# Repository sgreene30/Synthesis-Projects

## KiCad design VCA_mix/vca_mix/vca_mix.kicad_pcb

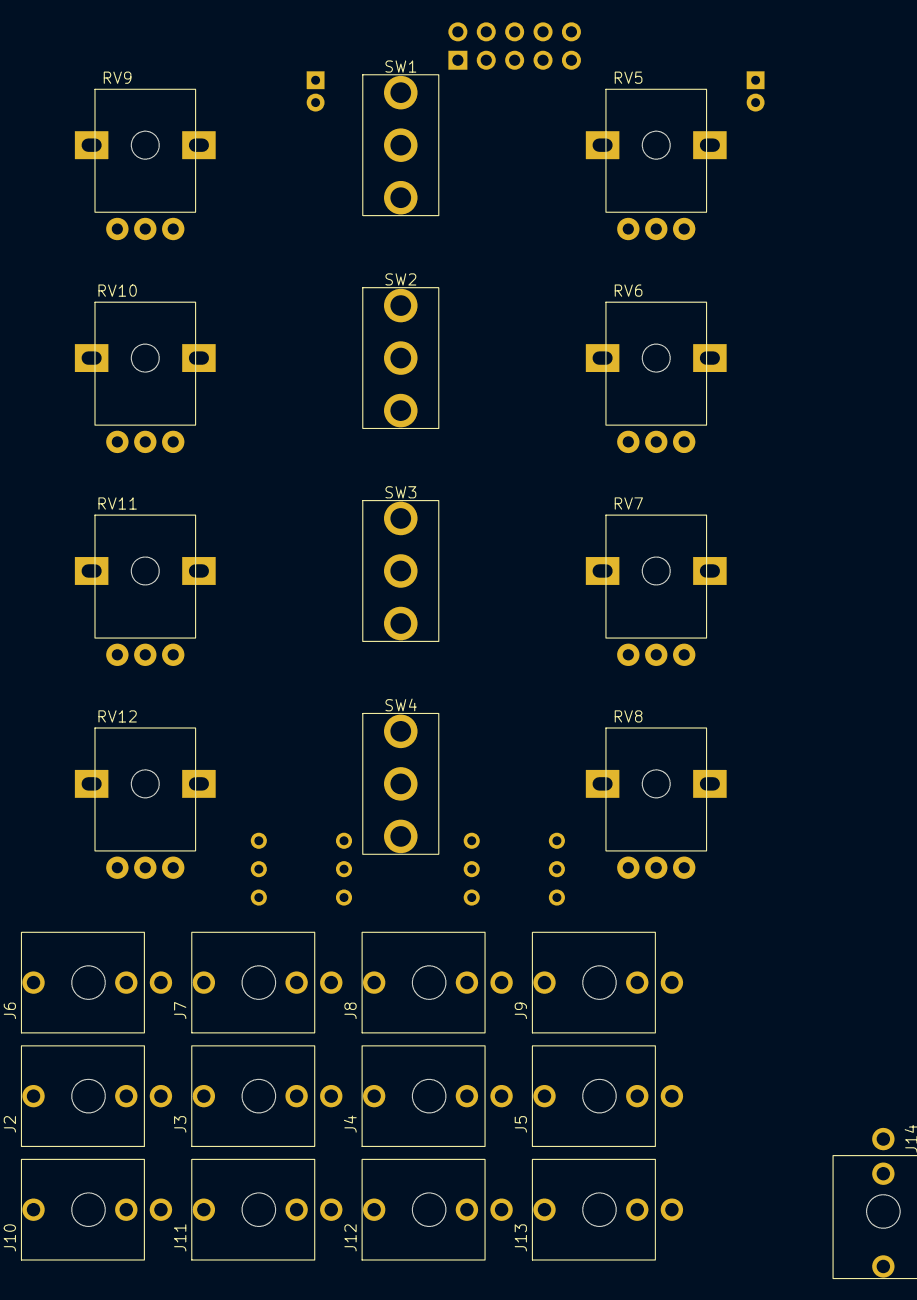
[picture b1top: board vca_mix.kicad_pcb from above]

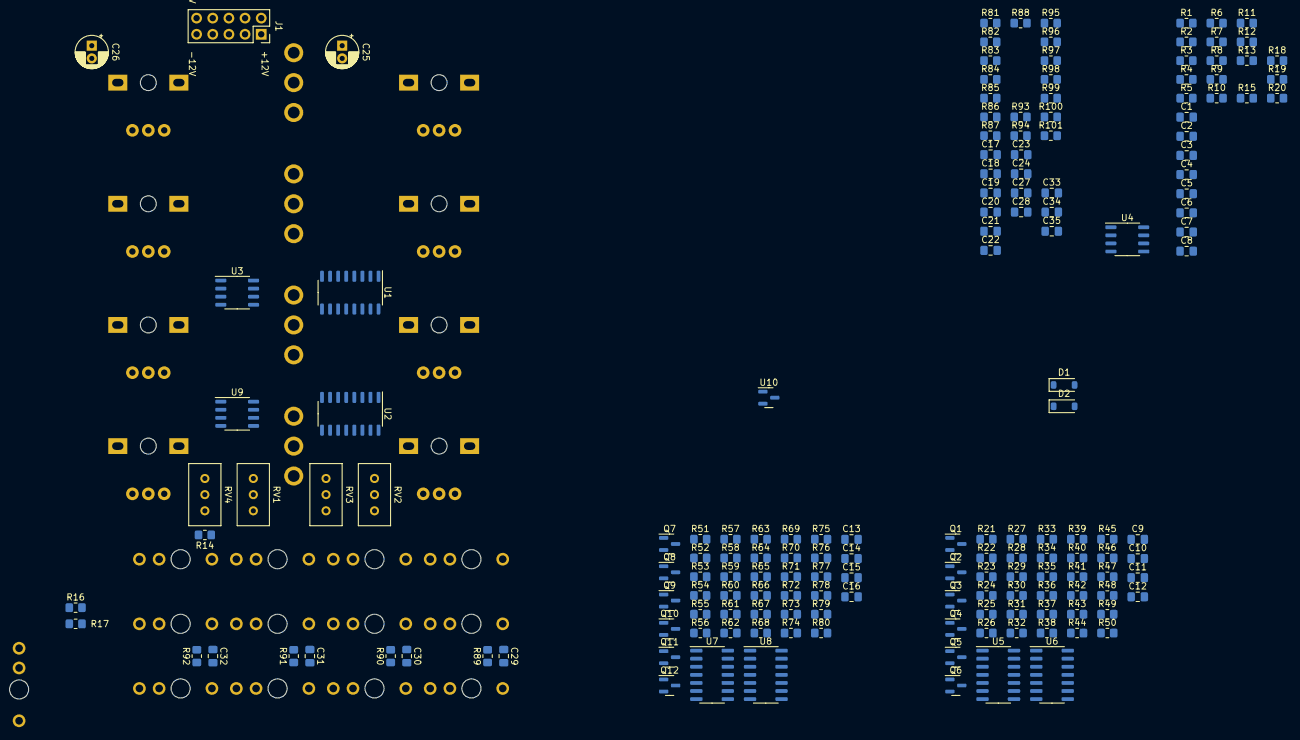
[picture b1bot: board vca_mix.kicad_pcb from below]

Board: 2 copper layers, 190 parts (165 on the bottom side), 128 nets, no tracks yet.

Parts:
C1, C2, C3, C4, C5, C6, C7, C8, C9, C10, C11, C12, C13, C14, C15, C16, C27, C28: 100n; C_0805_2012Metric_Pad1.18x1.45mm_HandSolder
C17, C18, C19, C20, C21, C22, C23, C24, C29, C30, C31, C32, C33: DNP; C_0805_2012Metric_Pad1.18x1.45mm_HandSolder
C25, C26: 10u; CP_Radial_D5.0mm_P2.00mm
C34, C35: 100p; C_0805_2012Metric_Pad1.18x1.45mm_HandSolder
D1: MBR0530-TP; D_SOD-123
D2: D_Schottky; D_SOD-123
J1: power; PinSocket_2x05_P2.54mm_Vertical
J2, J3, J4, J5, J6, J7, J8, J9, J10, J11, J12, J13, J14: Thonkiconn; thonkiconn
Q1, Q5, Q8, Q11: MMBT3904; SOT-23
Q2, Q3, Q4, Q6, Q7, Q9, Q10, Q12: MMBT3906; SOT-23
R1, R2, R11, R14, R31, R32, R34, R37, R46, R49, R52, R61, R64, R67, R76, R79, R98, R99: 20k; R_0805_2012Metric_Pad1.20x1.40mm_HandSolder
R3, R4, R5, R6, R12, R13, R16, R17: 430R; R_0805_2012Metric_Pad1.20x1.40mm_HandSolder
R7, R8, R15, R18, R24, R25, R28, R35, R39, R41, R48, R50, R54, R56, R63, R65, R69, R71, R78, R80, R94, R95, R96, R97, R100: 10k; R_0805_2012Metric_Pad1.20x1.40mm_HandSolder
R9, R10, R19, R20: 47k; R_0805_2012Metric_Pad1.20x1.40mm_HandSolder
R21, R23, R26, R38, R42, R45, R53, R57, R60, R68, R72, R75: 200k; R_0805_2012Metric_Pad1.20x1.40mm_HandSolder
R22, R43, R58, R73: 100k; R_0805_2012Metric_Pad1.20x1.40mm_HandSolder
R27, R44, R59, R74: 3k; R_0805_2012Metric_Pad1.20x1.40mm_HandSolder
R29, R40, R55, R70: 330; R_0805_2012Metric_Pad1.20x1.40mm_HandSolder
R30, R47, R62, R77: 120k; R_0805_2012Metric_Pad1.20x1.40mm_HandSolder
R33, R36, R51, R66: 6k2; R_0805_2012Metric_Pad1.20x1.40mm_HandSolder
R81, R82, R83, R84, R85, R86, R87, R88: 0R; R_0805_2012Metric_Pad1.20x1.40mm_HandSolder
R89, R90, R91, R92, R93: 100R; R_0805_2012Metric_Pad1.20x1.40mm_HandSolder
R101: 470; R_0805_2012Metric_Pad1.20x1.40mm_HandSolder
RV1, RV2, RV3, RV4: 100R; Potentiometer_Bourns_3296W_Vertical
RV5, RV6, RV7, RV8, RV9, RV10, RV11, RV12: 10k; alpha_pot
SW1, SW2, SW3, SW4: SW_SPDT; Mini_sw
U1, U2: LM13700; SO-16_3.9x9.9mm_P1.27mm
U3, U4, U9: TL072; SO-8_3.9x4.9mm_P1.27mm
U5, U6, U7, U8: TL074; SO-14_3.9x8.65mm_P1.27mm
U10: LM4040DBZ-3; SOT-23

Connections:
+3V0: R28.1, R33.1, R36.1, R39.1, R51.1, R54.1, R66.1, R69.1, R101.2, U10.1 (K)
+12V: C1.1, C3.1, C5.1, C7.1, C9.1, C11.1, C13.1, C15.1, C25.1, C27.1, D1.1 (K), Q1.3 (C), Q5.3 (C), Q8.3 (C), Q11.3 (C), R7.2, R8.2, R15.2, R18.2, R101.1, RV5.1, RV6.1, RV7.1, RV8.1, U1.11 (V+), U2.11 (V+), U3.8 (V+), U4.8 (V+), U5.4 (V+), U6.4 (V+), U7.4 (V+), U8.4 (V+), U9.8 (V+)
-12V: C2.2, C4.2, C6.2, C8.2, C10.2, C12.2, C14.2, C16.2, C26.2, C28.2, D2.2 (A), R30.1, R47.1, R62.1, R77.1, RV5.3, RV6.3, RV7.3, RV8.3, U1.6 (V-), U2.6 (V-), U3.4 (V-), U4.4 (V-), U5.11 (V-), U6.11 (V-), U7.11 (V-), U8.11 (V-), U9.4 (V-)
/IO/MIX_OUT: C33.1, C35.2, R93.2, R100.2, U9.7
/IO/VCA_1_MIX: J10.TN, R94.1
/IO/VCA_2_MIX: J11.TN, R95.1
/IO/VCA_3_MIX: J12.TN, R96.1
/IO/VCA_4_MIX: J13.TN, R97.1
/VC/EXP_IABC_1: R31.1, SW1.3 (C)
/VC/EXP_IABC_2: R49.1, SW2.3 (C)
/VC/LIN_IABC_1: Q3.3 (C), SW1.1 (A)
/VC/LIN_IABC_2: Q4.3 (C), SW2.1 (A)
/VC/VC_1: R25.2, R26.1, R32.1, R37.1, U5.7
/VC/VC_2: R38.1, R50.2, U6.7
/VC_2/EXP_IABC_3: R64.1, SW3.3 (C)
/VC_2/EXP_IABC_4: R79.1, SW4.3 (C)
/VC_2/LIN_IABC_3: Q7.3 (C), SW3.1 (A)
/VC_2/LIN_IABC_4: Q10.3 (C), SW4.1 (A)
/VC_2/VC_3: R52.1, R53.1, R65.2, U7.7
/VC_2/VC_4: R67.1, R68.1, R80.2, U8.7
GND: C1.2, C2.1, C3.2, C4.1, C5.2, C6.1, C7.2, C8.1, C9.2, C10.1, C11.2, C12.1, C13.2, C14.1, C15.2, C16.1, C17.2, C18.2, C19.2, C20.2, C21.2, C22.2, C23.2, C24.2, C25.2, C26.1, C27.2, C28.1, C29.2, C30.2, C31.2, C32.2, C33.2, J1.3, J1.4, J1.5, J1.6, J1.7, J1.8, J3.S, J4.S, J5.S, J7.S, J8.S, J9.S, J10.S, J11.S, J12.S, J13.S, Q2.2 (E), Q6.2 (E), Q9.2 (E), Q12.2 (E), R9.1, R10.1, R19.1, R20.1, R29.2, R34.1, R40.2, R46.1, R55.2, R61.1, R70.2, R76.1, RV1.2, RV2.2, RV3.2, RV4.2, RV9.3, RV10.3, RV11.3, RV12.3, U5.3 (+), U5.5 (+), U5.12 (+), U6.3 (+), U6.5 (+), U6.12 (+), U7.3 (+), U7.5 (+), U7.12 (+), U8.3 (+), U8.5 (+), U8.12 (+), U9.3 (+), U9.5 (+), U10.2 (A)
unnamed: C17.1, R81.2, RV9.1
unnamed: C18.1, R82.2, RV10.1
unnamed: C19.1, R83.2, RV11.1
unnamed: C20.1, R84.2, RV12.1
unnamed: C34.2, R98.2, R99.1, U9.1
unnamed: D1.2 (A), J1.1, J1.2
unnamed: D2.1 (K), J1.9, J1.10
unnamed: J3.T, R86.1
unnamed: J4.T, R87.1
unnamed: J5.T, R88.1
unnamed: J7.T, R82.1
unnamed: J8.T, R83.1
unnamed: J9.T, R84.1
unnamed: J10.T, R89.1
unnamed: J11.T, R90.1
unnamed: J12.T, R91.1
unnamed: J13.T, R92.1
unnamed: Q1.1 (B), R27.2, U5.8
unnamed: Q1.2 (E), Q2.1 (B), R30.2
unnamed: Q2.3 (C), R31.2
unnamed: Q3.1 (B), R35.2, U5.14
unnamed: Q3.2 (E), R34.2
unnamed: Q4.1 (B), R41.2, U6.14
unnamed: Q4.2 (E), R46.2
unnamed: Q5.1 (B), R44.2, U6.8
unnamed: Q5.2 (E), Q6.1 (B), R47.2
unnamed: Q6.3 (C), R49.2
unnamed: Q7.1 (B), R56.2, U7.14
unnamed: Q7.2 (E), R61.2
unnamed: Q8.1 (B), R59.2, U7.8
unnamed: Q8.2 (E), Q9.1 (B), R62.2
unnamed: Q9.3 (C), R64.2
unnamed: Q10.1 (B), R71.2, U8.14
unnamed: Q10.2 (E), R76.2
unnamed: Q11.1 (B), R74.2, U8.8
unnamed: Q11.2 (E), Q12.1 (B), R77.2
unnamed: Q12.3 (C), R79.2
unnamed: R3.1, RV1.1
unnamed: R4.2, RV1.3
unnamed: R5.1, RV2.1
unnamed: R6.2, RV2.3
unnamed: R12.1, RV3.1
unnamed: R13.2, RV3.3
unnamed: R16.1, RV4.1
unnamed: R17.2, RV4.3
unnamed: R21.1, RV5.2
unnamed: R23.2, R24.1, U5.1
unnamed: R42.1, RV6.2
unnamed: R45.2, R48.1, U6.1
unnamed: R57.1, RV7.2
unnamed: R60.2, R63.1, U7.1
unnamed: R72.1, RV8.2
unnamed: R75.2, R78.1, U8.1
unnamed: R6.1, U1.14 (+)
unnamed: R2.2, R5.2, U1.13 (-)
unnamed: R8.1, U1.15 (DIODE_BIAS)
unnamed: R13.1, U1.3 (+)
unnamed: R11.2, R12.2, U1.4 (-)
unnamed: R15.1, U1.2 (DIODE_BIAS)
unnamed: R4.1, U2.14 (+)
unnamed: R1.2, R3.2, U2.13 (-)
unnamed: R7.1, U2.15 (DIODE_BIAS)
unnamed: R17.1, U2.3 (+)
unnamed: R14.2, R16.2, U2.4 (-)
unnamed: R18.1, U2.2 (DIODE_BIAS)
unnamed: R10.2, U1.12, U3.3 (+)
unnamed: R19.2, U1.5, U3.5 (+)
unnamed: R9.2, U2.12, U4.3 (+)
unnamed: R20.2, U2.5, U4.5 (+)
unnamed: R21.2, R22.2, R23.1, U5.2 (-)
unnamed: R24.2, R25.1, U5.6 (-)
unnamed: R28.2, R29.1, U5.10 (+)
unnamed: R26.2, R27.1, U5.9 (-)
unnamed: R32.2, R33.2, R35.1, U5.13 (-)
unnamed: R42.2, R43.2, R45.1, U6.2 (-)
unnamed: R48.2, R50.1, U6.6 (-)
unnamed: R39.2, R40.1, U6.10 (+)
unnamed: R38.2, R44.1, U6.9 (-)
unnamed: R36.2, R37.2, R41.1, U6.13 (-)
unnamed: R57.2, R58.2, R60.1, U7.2 (-)
unnamed: R63.2, R65.1, U7.6 (-)
unnamed: R54.2, R55.1, U7.10 (+)
unnamed: R53.2, R59.1, U7.9 (-)
unnamed: R51.2, R52.2, R56.1, U7.13 (-)
unnamed: R72.2, R73.2, R75.1, U8.2 (-)
unnamed: R78.2, R80.1, U8.6 (-)
unnamed: R69.2, R70.1, U8.10 (+)
unnamed: R68.2, R74.1, U8.9 (-)
unnamed: R66.2, R67.2, R71.1, U8.13 (-)
unnamed: C34.1, R94.2, R95.2, R96.2, R97.2, R98.1, U9.2 (-)
unnamed: C35.1, R99.2, R100.1, U9.6 (-)
VCA_1_CV: R22.1, RV9.2
VCA_1_IABC: SW1.2 (B), U1.16
VCA_1_IN: C21.1, R2.1, R85.2
VCA_1_OUT: C29.1, R89.2, U3.1, U3.2 (-)
VCA_2_CV: R43.1, RV10.2
VCA_2_IABC: SW2.2 (B), U1.1
VCA_2_IN: C22.1, R11.1, R86.2
VCA_2_OUT: C30.1, R90.2, U3.6 (-), U3.7
VCA_3_CV: R58.1, RV11.2
VCA_3_IABC: SW3.2 (B), U2.16
VCA_3_IN: C23.1, R1.1, R87.2
VCA_3_OUT: C31.1, R91.2, U4.1, U4.2 (-)
VCA_4_CV: R73.1, RV12.2
VCA_4_IABC: SW4.2 (B), U2.1
VCA_4_IN: C24.1, R14.1, R88.2
VCA_4_OUT: C32.1, R92.2, U4.6 (-), U4.7
